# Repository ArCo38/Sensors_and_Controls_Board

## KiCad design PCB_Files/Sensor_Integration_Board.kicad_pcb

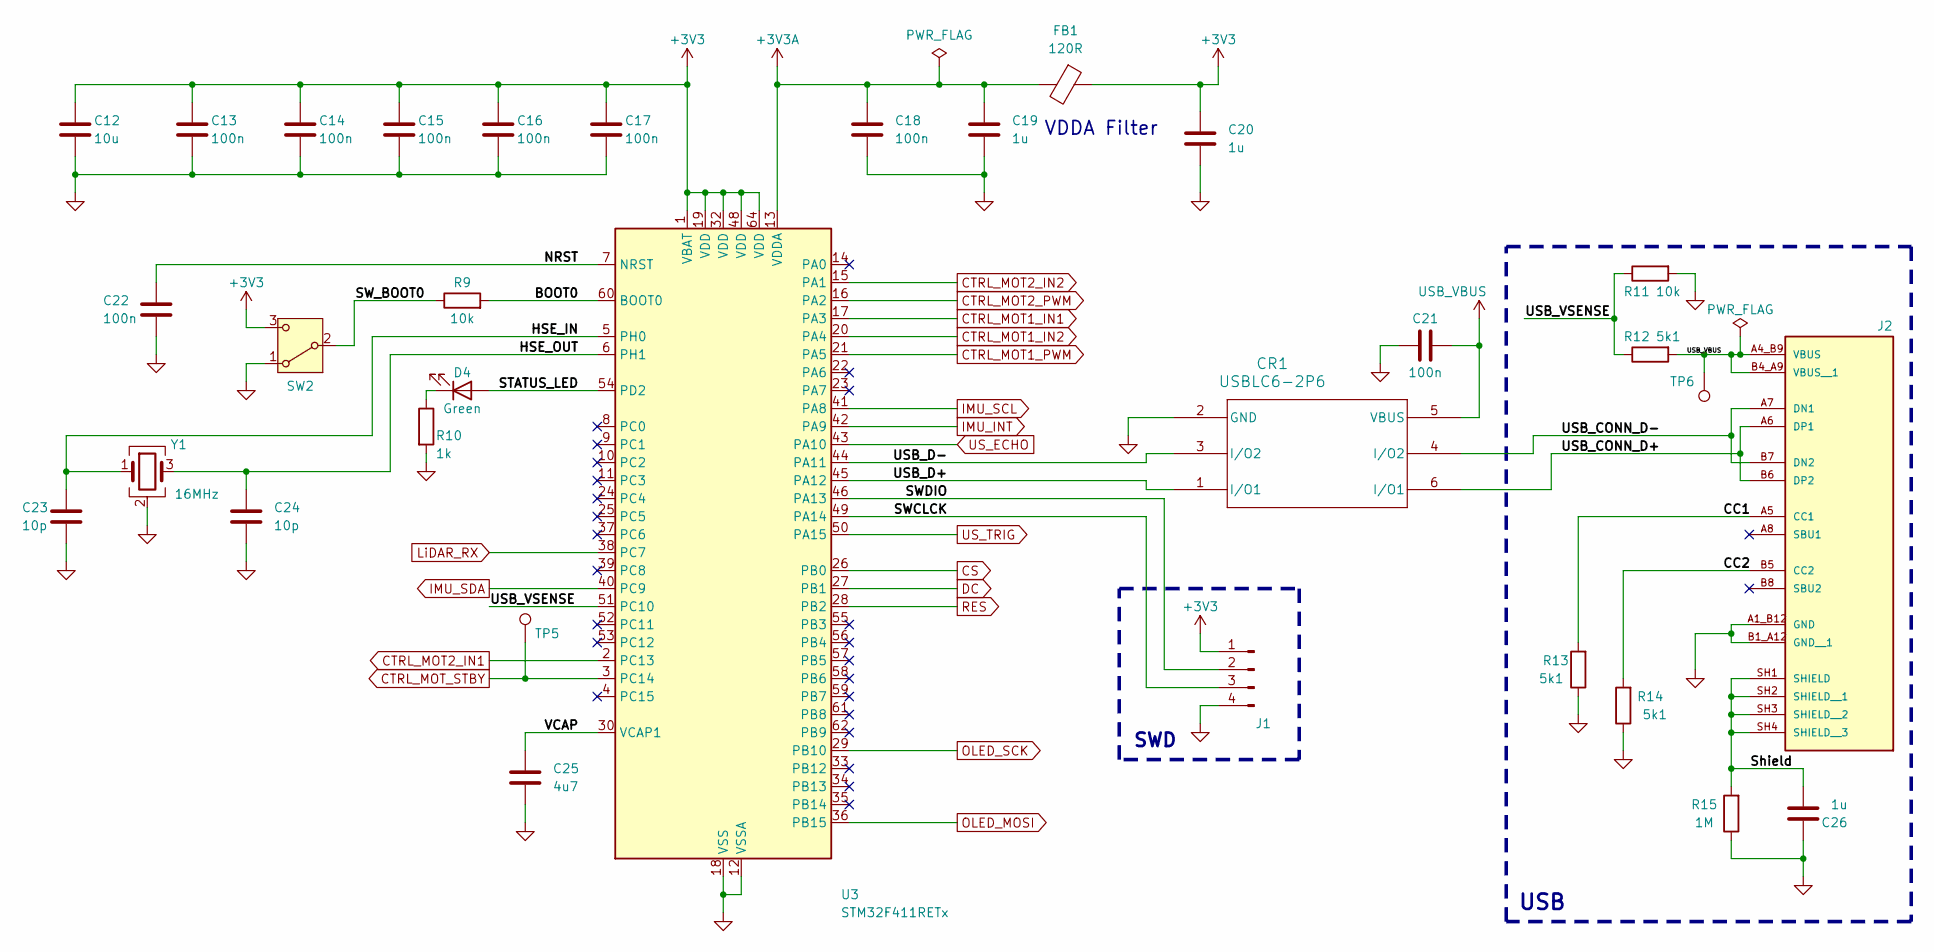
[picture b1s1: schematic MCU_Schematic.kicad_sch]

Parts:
C12: 10u; C_0805_2012Metric
C13, C14, C15, C16, C17, C18, C21, C22: 100n; C_0603_1608Metric
C19, C20, C26: 1u; C_0805_2012Metric
C23, C24: 10p; C_0603_1608Metric
C25: 4u7; C_0805_2012Metric
CR1: USBLC6-2P6; SOT-666_STM
D4: Green; LED_0603_1608Metric
FB1: 120R; L_0603_1608Metric
J1: SWD; PinHeader_1x04_P2.54mm_Vertical
J2: UJ20-C-H-G-SMT-4-P16-TR; CUSTOM_OVERHANG_SAMESKY_UJ20-C-H-G-SMT-4-P16-TR; PARTREV 1.0
R9, R11: 10k; R_0603_1608Metric
R10: 1k; R_0603_1608Metric
R12, R13, R14: 5k1; R_0603_1608Metric
R15: 1M; R_0603_1608Metric
SW2: SW_SPDT; SW_1218_EWI
TP5, TP6: TestPoint; TestPoint_Pad_D1.0mm
U3: STM32F411RETx; LQFP-64_10x10mm_P0.5mm
Y1: 16MHz; Crystal_SMD_SeikoEpson_TSX3225-4Pin_3.2x2.5mm

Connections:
+3V3: C12.1, C13.1, C14.1, C15.1, C16.1, C17.1, C20.1, FB1.1, J1.1, SW2.3 (C), U3.1 (VBAT), U3.19 (VDD), U3.32 (VDD), U3.48 (VDD), U3.64 (VDD); also elsewhere on the board
+3V3A: C18.1, C19.1, FB1.2, U3.13 (VDDA)
/MicroController - USB - SWD/BOOT0: R9.2, U3.60 (BOOT0)
/MicroController - USB - SWD/CC1: J2.A5 (CC1), R13.2
/MicroController - USB - SWD/CC2: J2.B5 (CC2), R14.2
/MicroController - USB - SWD/HSE_IN: C23.1, U3.5 (PH0), Y1.1
/MicroController - USB - SWD/HSE_OUT: C24.1, U3.6 (PH1), Y1.3
/MicroController - USB - SWD/NRST: C22.1, U3.7 (NRST)
/MicroController - USB - SWD/STATUS_LED: D4.2 (A), U3.54 (PD2)
/MicroController - USB - SWD/SWCLCK: J1.3, U3.49 (PA14)
/MicroController - USB - SWD/SWDIO: J1.2, U3.46 (PA13)
/MicroController - USB - SWD/SW_BOOT0: R9.1, SW2.2 (B)
/MicroController - USB - SWD/Shield: C26.1, J2.SH1 (SHIELD), J2.SH2 (SHIELD__1), J2.SH3 (SHIELD__2), J2.SH4 (SHIELD__3), R15.2
/MicroController - USB - SWD/USB_CONN_D+: CR1.6 (I/O1), J2.A6 (DP1), J2.B6 (DP2)
/MicroController - USB - SWD/USB_CONN_D-: CR1.4 (I/O2), J2.A7 (DN1), J2.B7 (DN2)
/MicroController - USB - SWD/USB_D+: CR1.1 (I/O1), U3.45 (PA12)
/MicroController - USB - SWD/USB_D-: CR1.3 (I/O2), U3.44 (PA11)
/MicroController - USB - SWD/USB_VSENSE: R11.1, R12.1, U3.51 (PC10)
/MicroController - USB - SWD/VCAP: C25.2, U3.30 (VCAP1)
CS: U3.26 (PB0); also elsewhere on the board
CTRL_MOT1_IN1: U3.17 (PA3); also elsewhere on the board
CTRL_MOT1_IN2: U3.20 (PA4); also elsewhere on the board
CTRL_MOT1_PWM: U3.21 (PA5); also elsewhere on the board
CTRL_MOT2_IN1: U3.2 (PC13); also elsewhere on the board
CTRL_MOT2_IN2: U3.15 (PA1); also elsewhere on the board
CTRL_MOT2_PWM: U3.16 (PA2); also elsewhere on the board
CTRL_MOT_STBY: TP5.1 (1_1), U3.3 (PC14); also elsewhere on the board
DC: U3.27 (PB1); also elsewhere on the board
GND: C12.2, C13.2, C14.2, C15.2, C16.2, C17.2, C18.2, C19.2, C20.2, C21.1, C22.2, C23.2, C24.2, C25.1, C26.2, CR1.2 (GND), J1.4, J2.A1_B12 (GND), J2.B1_A12 (GND__1), R10.2, R11.2, R13.1, R14.1, R15.1, SW2.1 (A), U3.12 (VSSA), U3.18 (VSS), U3.31 (VSS), U3.47 (VSS), U3.63 (VSS), Y1.2 (G), Y1.4 (G); also elsewhere on the board
IMU_INT: U3.42 (PA9); also elsewhere on the board
IMU_SCL: U3.41 (PA8); also elsewhere on the board
IMU_SDA: U3.40 (PC9); also elsewhere on the board
LiDAR_RX: U3.38 (PC7); also elsewhere on the board
unnamed: D4.1 (K), R10.1
OLED_MOSI: U3.36 (PB15); also elsewhere on the board
OLED_SCK: U3.29 (PB10); also elsewhere on the board
RES: U3.28 (PB2); also elsewhere on the board
USB_VBUS: C21.2, CR1.5 (VBUS), J2.A4_B9 (VBUS), J2.B4_A9 (VBUS__1), R12.2, TP6.1 (1_1)
US_ECHO: U3.43 (PA10); also elsewhere on the board
US_TRIG: U3.50 (PA15); also elsewhere on the board

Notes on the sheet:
USB
SWD
VDDA Filter

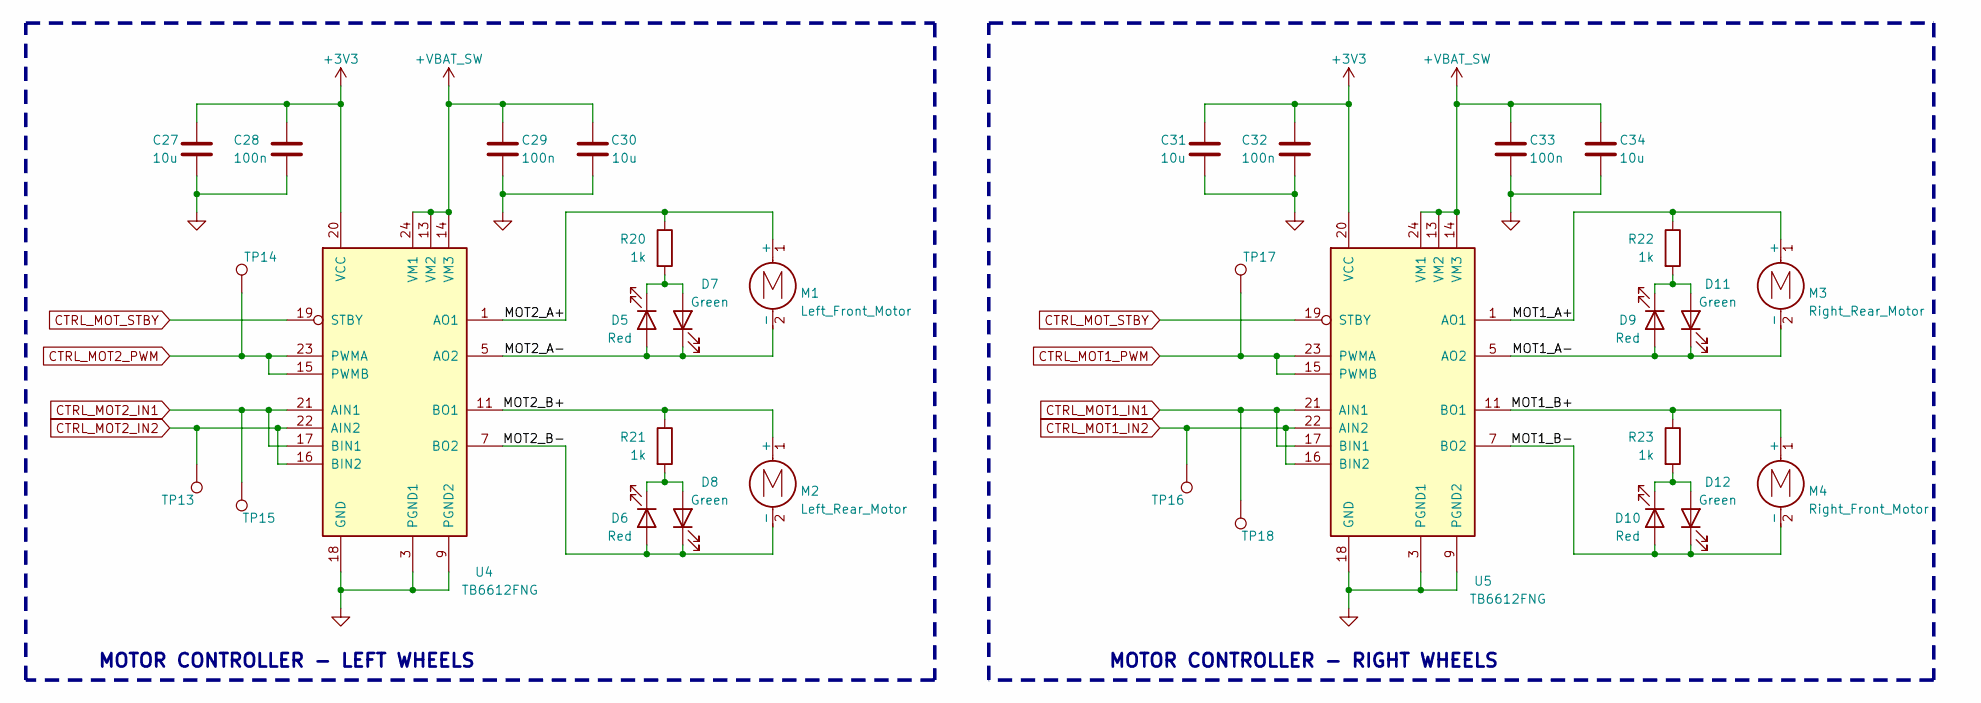
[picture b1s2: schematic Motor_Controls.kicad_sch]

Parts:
C27, C30, C31, C34: 10u; C_0805_2012Metric
C28, C29, C32, C33: 100n; C_0603_1608Metric
D5, D6, D9, D10: Red; LED_0603_1608Metric
D7, D8, D11, D12: Green; LED_0603_1608Metric
M1: Left_Front_Motor; JST_XH_B2B-XH-A_1x02_P2.50mm_Vertical
M2: Left_Rear_Motor; JST_XH_B2B-XH-A_1x02_P2.50mm_Vertical
M3: Right_Rear_Motor; JST_XH_B2B-XH-A_1x02_P2.50mm_Vertical
M4: Right_Front_Motor; JST_XH_B2B-XH-A_1x02_P2.50mm_Vertical
R20, R21, R22, R23: 1k; R_0603_1608Metric
TP13, TP14, TP15, TP16, TP17, TP18: TestPoint; TestPoint_Pad_D1.0mm
U4, U5: TB6612FNG; SSOP-24_5.3x8.2mm_P0.65mm

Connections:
+3V3: C27.1, C28.1, C31.1, C32.1, U4.20 (VCC), U5.20 (VCC); also elsewhere on the board
+VBAT_SW: C29.1, C30.1, C33.1, C34.1, U4.13 (VM2), U4.14 (VM3), U4.24 (VM1), U5.13 (VM2), U5.14 (VM3), U5.24 (VM1); also elsewhere on the board
/Motor_Controls/MOT1_A+: M3.1 (+), R22.1, U5.1 (AO1), U5.2 (AO1)
/Motor_Controls/MOT1_A-: D9.2 (A), D11.1 (K), M3.2 (-), U5.5 (AO2), U5.6 (AO2)
/Motor_Controls/MOT1_B+: M4.1 (+), R23.1, U5.11 (BO1), U5.12 (BO1)
/Motor_Controls/MOT1_B-: D10.2 (A), D12.1 (K), M4.2 (-), U5.7 (BO2), U5.8 (BO2)
/Motor_Controls/MOT2_A+: M1.1 (+), R20.1, U4.1 (AO1), U4.2 (AO1)
/Motor_Controls/MOT2_A-: D5.2 (A), D7.1 (K), M1.2 (-), U4.5 (AO2), U4.6 (AO2)
/Motor_Controls/MOT2_B+: M2.1 (+), R21.1, U4.11 (BO1), U4.12 (BO1)
/Motor_Controls/MOT2_B-: D6.2 (A), D8.1 (K), M2.2 (-), U4.7 (BO2), U4.8 (BO2)
CTRL_MOT1_IN1: TP18.1 (1_1), U5.17 (BIN1), U5.21 (AIN1); also elsewhere on the board
CTRL_MOT1_IN2: TP16.1 (1_1), U5.16 (BIN2), U5.22 (AIN2); also elsewhere on the board
CTRL_MOT1_PWM: TP17.1 (1_1), U5.15 (PWMB), U5.23 (PWMA); also elsewhere on the board
CTRL_MOT2_IN1: TP15.1 (1_1), U4.17 (BIN1), U4.21 (AIN1); also elsewhere on the board
CTRL_MOT2_IN2: TP13.1 (1_1), U4.16 (BIN2), U4.22 (AIN2); also elsewhere on the board
CTRL_MOT2_PWM: TP14.1 (1_1), U4.15 (PWMB), U4.23 (PWMA); also elsewhere on the board
CTRL_MOT_STBY: U4.19 (STBY), U5.19 (STBY); also elsewhere on the board
GND: C27.2, C28.2, C29.2, C30.2, C31.2, C32.2, C33.2, C34.2, U4.3 (PGND1), U4.4 (PGND1), U4.9 (PGND2), U4.10 (PGND2), U4.18 (GND), U5.3 (PGND1), U5.4 (PGND1), U5.9 (PGND2), U5.10 (PGND2), U5.18 (GND); also elsewhere on the board
unnamed: D5.1 (K), D7.2 (A), R20.2
unnamed: D6.1 (K), D8.2 (A), R21.2
unnamed: D10.1 (K), D12.2 (A), R23.2
unnamed: D9.1 (K), D11.2 (A), R22.2

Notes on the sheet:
MOTOR CONTROLLER - LEFT WHEELS
MOTOR CONTROLLER - RIGHT WHEELS

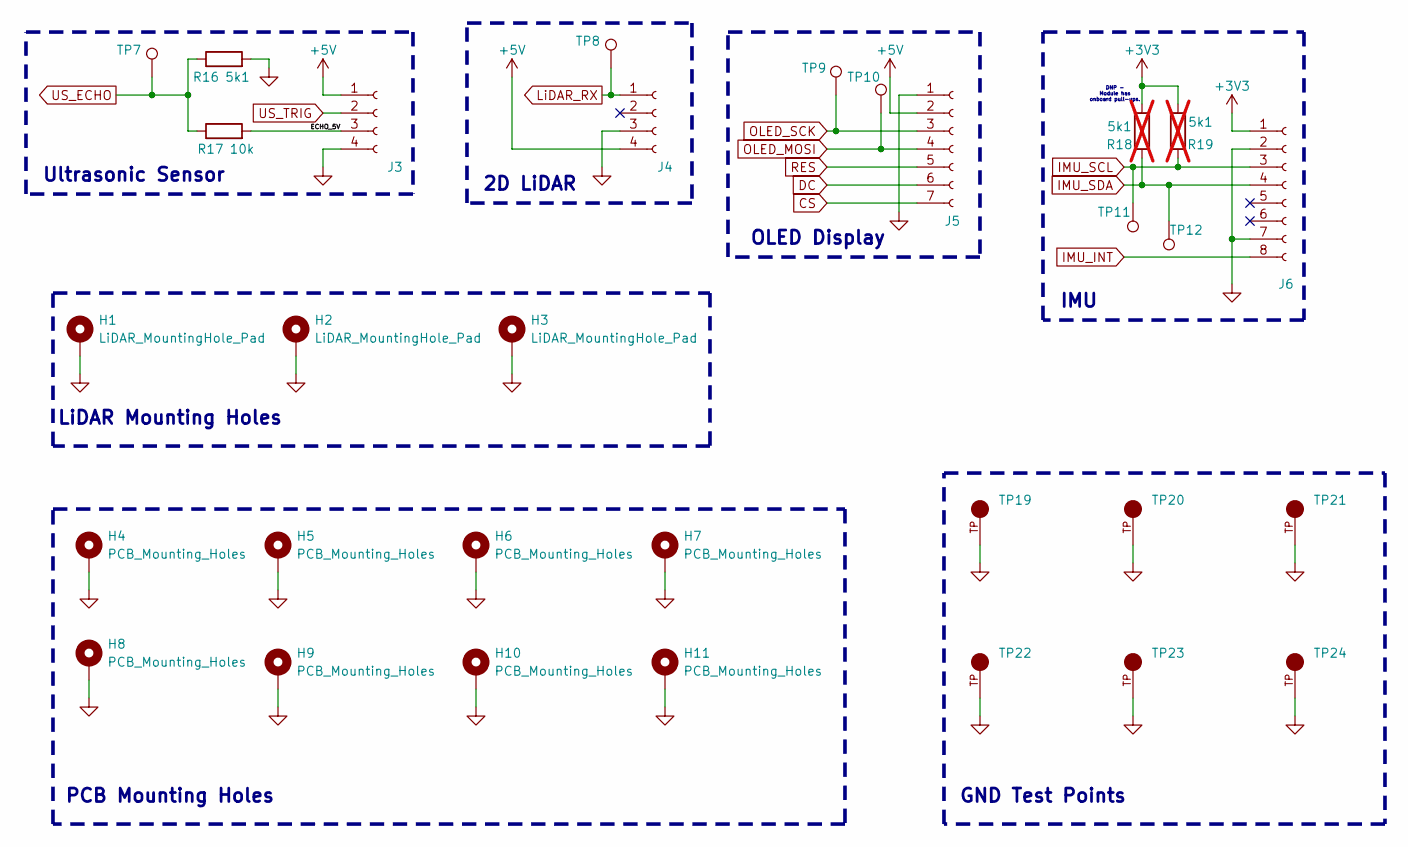
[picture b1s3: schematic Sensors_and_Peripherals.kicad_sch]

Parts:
H1, H2, H3: LiDAR_MountingHole_Pad; MountingHole_2.7mm_Pad_Via
H4, H5, H6, H7, H8, H9, H10, H11: PCB_Mounting_Holes; MountingHole_3.2mm_M3_Pad_Via
J3: Ultrasonic_Sensor; PinSocket_1x04_P2.54mm_Vertical
J4: 2D_LiDAR; B4B-ZR
J5: OLED_Display; PinSocket_1x07_P2.54mm_Vertical
J6: IMU; PinSocket_1x08_P2.54mm_Vertical
R16: 5k1; R_0603_1608Metric
R17: 10k; R_0603_1608Metric
R18, R19: 5k1; R_0603_1608Metric; not fitted
TP7, TP8, TP9, TP10, TP11, TP12: TestPoint; TestPoint_Pad_D1.0mm
TP19: 5001; KEYSTONE_5001; MPN 5001
TP20, TP21, TP22, TP23, TP24: 5001; KEYSTONE_5001

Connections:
+3V3: J6.1, R18.1, R19.1; also elsewhere on the board
+5V: J3.1, J4.4, J5.2; also elsewhere on the board
/Sensors_and_Peripherals/ECHO_5V: J3.3, R17.2
CS: J5.7; also elsewhere on the board
DC: J5.6; also elsewhere on the board
GND: H1.1 (1_1), H2.1 (1_1), H3.1 (1_1), H4.1 (1_1), H5.1 (1_1), H6.1 (1_1), H7.1 (1_1), H8.1 (1_1), H9.1 (1_1), H10.1 (1_1), H11.1 (1_1), J3.4, J4.3, J5.1, J6.2, J6.7, R16.2, TP19.TP, TP20.TP, TP21.TP, TP22.TP, TP23.TP, TP24.TP; also elsewhere on the board
IMU_INT: J6.8; also elsewhere on the board
IMU_SCL: J6.3, R19.2, TP11.1 (1_1); also elsewhere on the board
IMU_SDA: J6.4, R18.2, TP12.1 (1_1); also elsewhere on the board
LiDAR_RX: J4.1, TP8.1 (1_1); also elsewhere on the board
OLED_MOSI: J5.4, TP10.1 (1_1); also elsewhere on the board
OLED_SCK: J5.3, TP9.1 (1_1); also elsewhere on the board
RES: J5.5; also elsewhere on the board
US_ECHO: R16.1, R17.1, TP7.1 (1_1); also elsewhere on the board
US_TRIG: J3.2; also elsewhere on the board

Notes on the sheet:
2D LiDAR
GND Test Points
IMU
OLED Display
LiDAR Mounting Holes
Ultrasonic Sensor
PCB Mounting Holes
DNP - Module has onboard pull-ups.

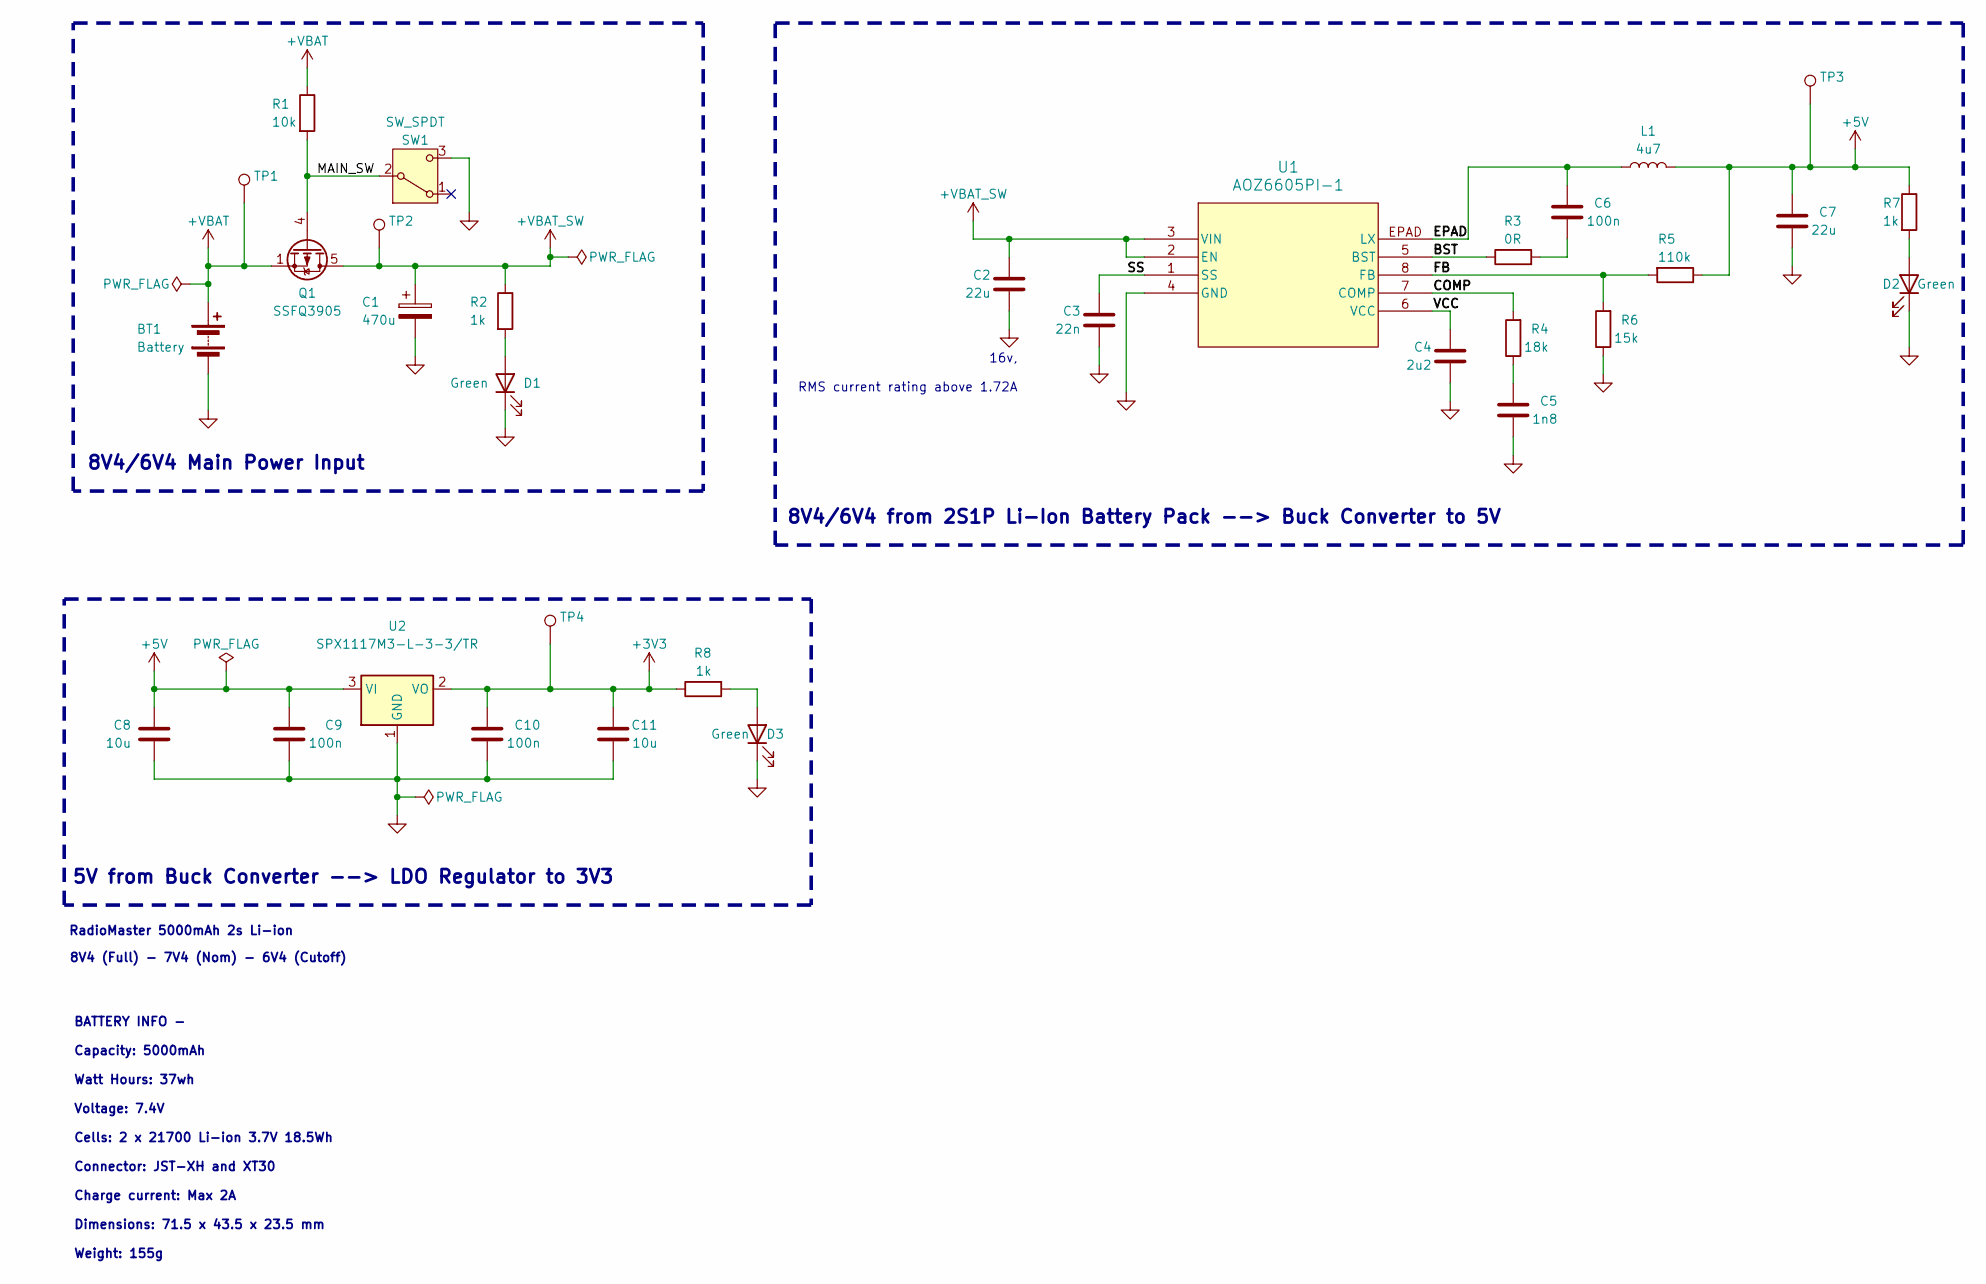
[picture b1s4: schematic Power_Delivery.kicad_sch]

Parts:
BT1: Battery; AMASS_XT30UPB-M_1x02_P5.0mm_Vertical
C1: 470u; CP_Radial_D10.0mm_P5.00mm
C2, C7: 22u; C_0805_2012Metric
C3: 22n; C_0603_1608Metric
C4: 2u2; C_0805_2012Metric
C5: 1n8; C_0603_1608Metric
C6, C9, C10: 100n; C_0603_1608Metric
C8, C11: 10u; C_0805_2012Metric
D1, D2, D3: Green; LED_0603_1608Metric
L1: 4u7; L_0603_1608Metric
Q1: SSFQ3905; SOIC-8_3.9x4.9mm_P1.27mm
R1: 10k; R_0603_1608Metric
R2, R7, R8: 1k; R_0603_1608Metric
R3: 0R; R_0603_1608Metric
R4: 18k; R_0603_1608Metric
R5: 110k; R_0603_1608Metric
R6: 15k; R_0603_1608Metric
SW1: SW_SPDT; SW_1218_EWI
TP1, TP2, TP3, TP4: TestPoint; TestPoint_Pad_D1.0mm
U1: AOZ6605PI-1; SO8_EP1_AOS
U2: SPX1117M3-L-3-3/TR; SOT-223-3_TabPin2

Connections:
+3V3: C10.1, C11.1, R8.1, TP4.1 (1_1), U2.2 (VO); also elsewhere on the board
+5V: C7.1, C8.1, C9.1, L1.2, R5.1, R7.1, TP3.1 (1_1), U2.3 (VI); also elsewhere on the board
+VBAT: BT1.1 (+), Q1.1 (S), Q1.2 (S), Q1.3 (S), R1.1, TP1.1 (1_1)
+VBAT_SW: C1.1, C2.1, Q1.5 (D), Q1.6 (D), Q1.7 (D), Q1.8 (D), R2.1, TP2.1 (1_1), U1.2 (EN), U1.3 (VIN); also elsewhere on the board
/Power_Delivery/BST: R3.1, U1.5 (BST)
/Power_Delivery/COMP: R4.2, U1.7 (COMP)
/Power_Delivery/EPAD: C6.2, L1.1, U1.EPAD (LX)
/Power_Delivery/FB: R5.2, R6.2, U1.8 (FB)
/Power_Delivery/MAIN_SW: Q1.4 (G), R1.2, SW1.2 (B)
/Power_Delivery/SS: C3.1, U1.1 (SS)
/Power_Delivery/VCC: C4.1, U1.6 (VCC)
GND: BT1.2 (-), C1.2, C2.2, C3.2, C4.2, C5.2, C7.2, C8.2, C9.2, C10.2, C11.2, D1.1 (K), D2.1 (K), D3.1 (K), R6.1, SW1.3 (C), U1.4 (GND), U2.1 (GND); also elsewhere on the board
unnamed: C5.1, R4.1
unnamed: C6.1, R3.2
unnamed: D1.2 (A), R2.2
unnamed: D2.2 (A), R7.2
unnamed: D3.2 (A), R8.2

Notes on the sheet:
8V4 (Full) - 7V4 (Nom) - 6V4 (Cutoff)
5V from Buck Converter --> LDO Regulator to 3V3
8V4/6V4 Main Power Input
RadioMaster 5000mAh 2s Li-ion
16v, RMS current rating above 1.72A
BATTERY INFO - Capacity: 5000mAh Watt Hours: 37wh Voltage: 7.4V Cells: 2 x 21700 Li-ion 3.7V 18.5Wh Connector: JST-XH and XT30 Charge current: Max 2A Dimensions: 71.5 x 43.5 x 23.5 mm Weight: 155g
8V4/6V4 from 2S1P Li-Ion Battery Pack --> Buck Converter to 5V

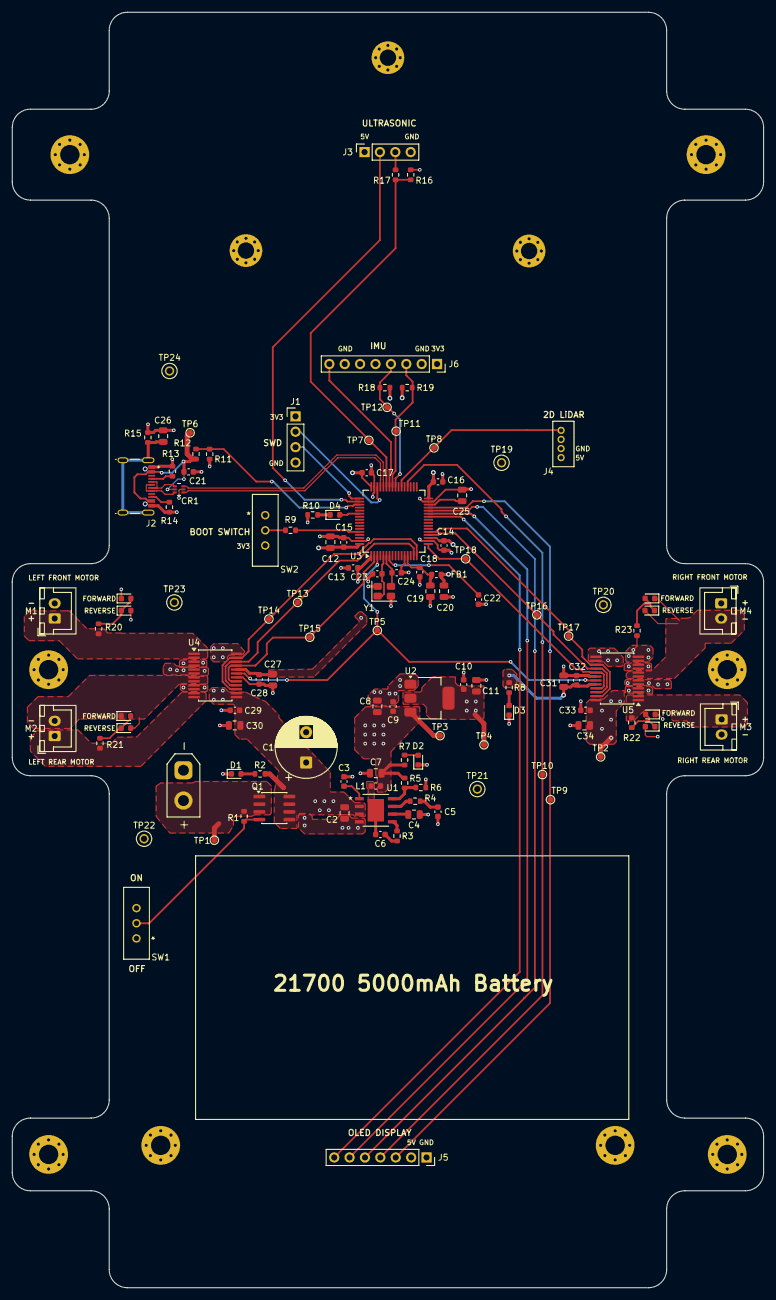
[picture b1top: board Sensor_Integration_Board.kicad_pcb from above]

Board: 4 copper layers, 124.0 x 210.5 mm, 127 parts (0 on the bottom side), 68 nets.

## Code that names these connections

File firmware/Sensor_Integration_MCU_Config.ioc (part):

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Mcu.Name=STM32F411R(C-E)Tx
Mcu.Package=LQFP64
Mcu.UserName=STM32F411RETx
PA10.Signal=S_TIM1_CH3
PA11.Mode=Device_Only
PA11.Signal=USB_OTG_FS_DM
PA12.Mode=Device_Only
PA12.Signal=USB_OTG_FS_DP
PA13.Mode=Serial_Wire
PA13.Signal=SYS_JTMS-SWDIO
PA14.Mode=Serial_Wire
PA14.Signal=SYS_JTCK-SWCLK
PA2.Signal=S_TIM2_CH3
PA5.Signal=S_TIM2_CH1_ETR
PA8.Mode=I2C
PA8.Signal=I2C3_SCL
PB10.GPIOParameters=GPIO_Speed
PB10.GPIO_Speed=GPIO_SPEED_FREQ_MEDIUM
PB10.Mode=TX_Only_Simplex_Unidirect_Master
PB10.Signal=SPI2_SCK
PB15.GPIOParameters=GPIO_Speed
PB15.GPIO_Speed=GPIO_SPEED_FREQ_MEDIUM
PB15.Mode=TX_Only_Simplex_Unidirect_Master
PB15.Signal=SPI2_MOSI
PC6.Mode=Asynchronous
PC6.Signal=USART6_TX
PC7.Mode=Asynchronous
PC7.Signal=USART6_RX
PC9.Mode=I2C
PC9.Signal=I2C3_SDA
PH0\ -\ OSC_IN.Mode=HSE-External-Oscillator
PH0\ -\ OSC_IN.Signal=RCC_OSC_IN
PH1\ -\ OSC_OUT.Mode=HSE-External-Oscillator
PH1\ -\ OSC_OUT.Signal=RCC_OSC_OUT
RCC.HSE_VALUE=16000000
RCC.SYSCLKFreq_VALUE=96000000
RCC.SYSCLKSource=RCC_SYSCLKSOURCE_PLLCLK
board=custom
